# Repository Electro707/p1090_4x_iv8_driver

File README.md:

# P1090 - IV-8 Driver, 4x
\> PCBs (both), Rev 1
\> Firmware, Rev 1A (wip)
\> Enclosure, Rev 1

This project is a driver for 4xIV-8 VFD Tubes.

# Directory Structure
- E1091: PCB, Driver board, KiCAD
- E1092: PCB, IV-8 Adapter Board, KiCAD
- F1093: Firmware, Arduino-IDE
- CAD: Enclosure, FreeCAD. All parts are under `C1094.FCStd`
    - C1094: Bottom Enclosure
    - C1095: Top Enclosure
    - C1096: Button Press Extender
    - C1097: Light Pipe for LED
- `release`: Latest exported build files, includes Schematic, BOM, Gerber, and STL files

# Firmware Doc

The document for the firmware can be found over at [https://electro707.com/documentation/Projects/F1093_docs/](https://electro707.com/documentation/Projects/F1093_docs/)

The document also describes the requirements for building the Firmware through the Arduino IDE.

To build the firmware, you will need to make a file `wifiDefault.h` in the firmrware's folder with the following WIFI credentials

```c
#ifndef WIFI_DEFAULT_H
#define WIFI_DEFAULT_H

#define DEFAULT_WIFI_SSID       "ENTER-SSID"
#define DEFAULT_WIFI_PASSWORD   "ENTER_PASS"

#endif
```

# Known Issues
> [!IMPORTANT]
> Please read the file linked below before attempting to build this hardware.

Known issues, and any workarounds, are documented in [ERRATA.md](ERRATA.md).

# todo:
- Buy or 3D print light-pipes for better LED-to-IV8 conductance

# License
This project is licensed under [GPLv3](LICENSE.md)**

** This excludes the files in `E1091_PCB_Driver/ExternalStep`, as they came from the manufacturer.

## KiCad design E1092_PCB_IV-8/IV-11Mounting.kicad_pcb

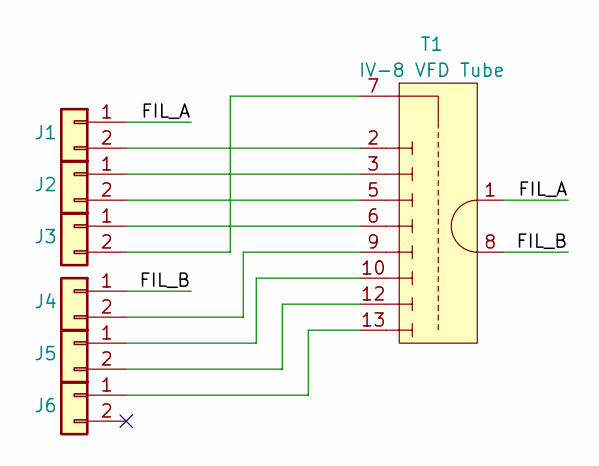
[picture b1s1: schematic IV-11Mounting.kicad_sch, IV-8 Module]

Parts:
J1, J2, J3, J4, J5, J6: Conn_01x02; PinHeader_1x02_P2.54mm_Vertical
T1: IV-8 VFD Tube; IV-8 VFD

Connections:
/FIL_A: J1.1, T1.1
/FIL_B: J4.1, T1.8
unnamed: J1.2, T1.2
unnamed: J2.1, T1.3
unnamed: J2.2, T1.5
unnamed: J3.1, T1.6
unnamed: J3.2, T1.7
unnamed: J4.2, T1.9
unnamed: J5.1, T1.10
unnamed: J5.2, T1.12
unnamed: J6.1, T1.13

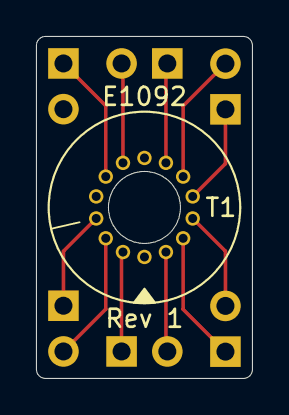
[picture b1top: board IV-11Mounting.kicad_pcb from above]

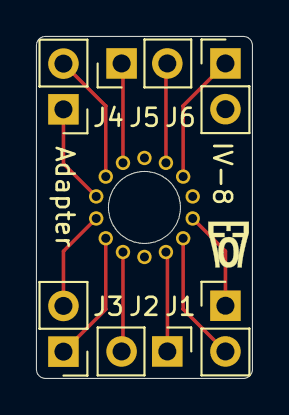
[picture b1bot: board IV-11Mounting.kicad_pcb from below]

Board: 2 copper layers, 12.0 x 19.0 mm, 7 parts (6 on the bottom side), 11 nets.

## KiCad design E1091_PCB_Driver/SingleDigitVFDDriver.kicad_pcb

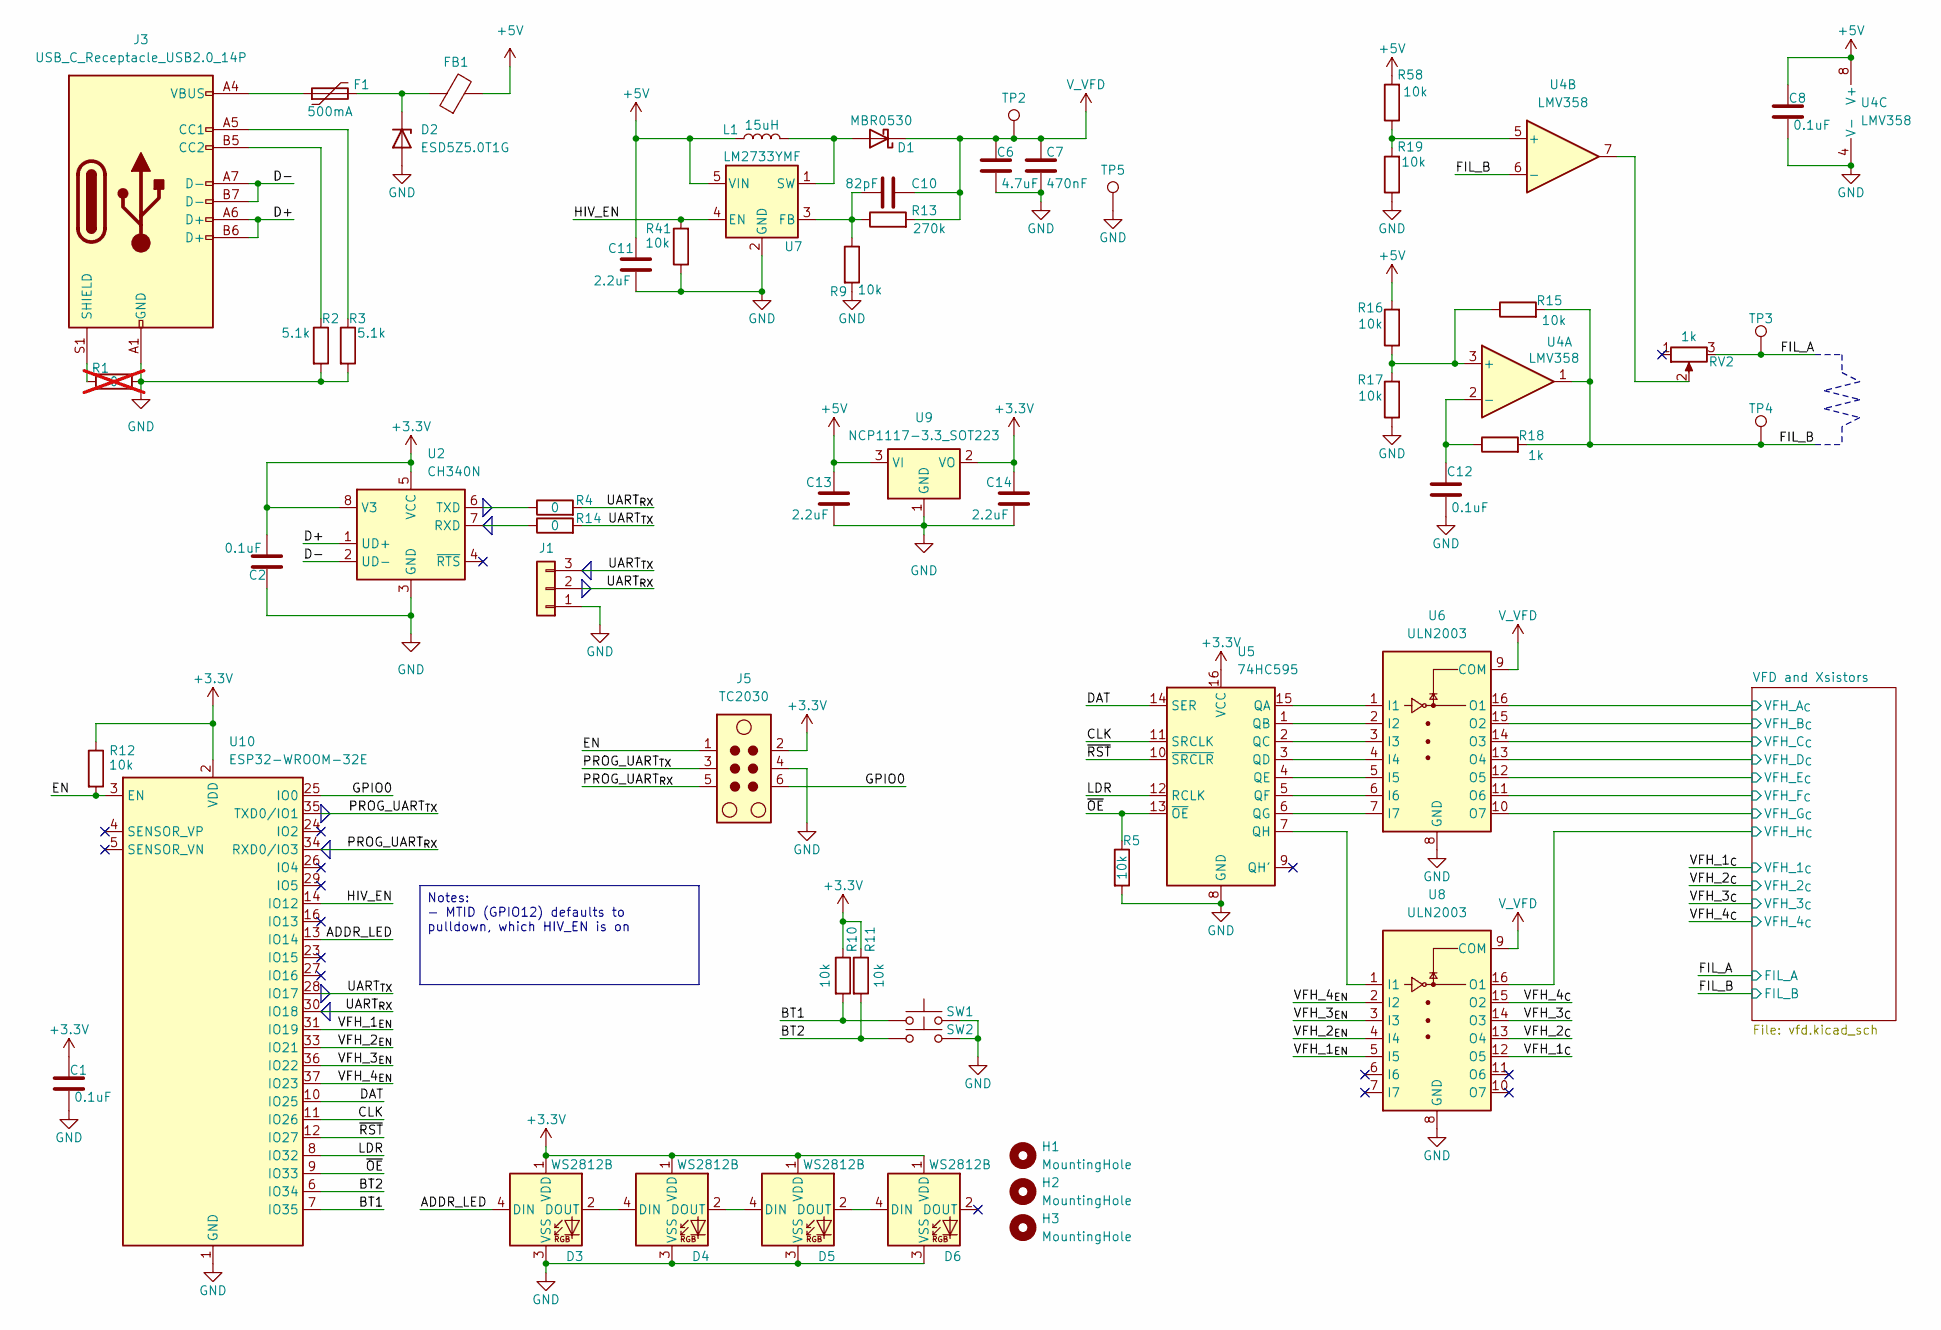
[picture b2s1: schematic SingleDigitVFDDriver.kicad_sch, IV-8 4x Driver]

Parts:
C1, C2, C8, C12: 0.1uF; C_0805_2012Metric
C6: 4.7uF; C_1206_3216Metric
C7: 470nF; C_0805_2012Metric
C10: 82pF; C_0805_2012Metric
C11, C13, C14: 2.2uF; C_0805_2012Metric
D1: MBR0530; D_SOD-123
D2: ESD5Z5.0T1G; D_SOD-523
D3, D4, D5, D6: WS2812B; LED_WS2812B_PLCC4_5.0x5.0mm_P3.2mm
F1: 500mA; Fuse_1206_3216Metric
FB1: FerriteBead; L_0805_2012Metric
H1, H2, H3: MountingHole; MountingHole_3.2mm_M3_DIN965
J1: Conn_01x03; PinSocket_1x03_P2.54mm_Vertical
J3: USB_C_Receptacle_USB2.0_14P; USB_C_Receptacle_GCT_USB4085
J5: TC2030; Tag-Connect_TC2030-IDC-NL_2x03_P1.27mm_Vertical
L1: 15uH; L_1210_3225Metric
R1: 0; R_0805_2012Metric; not fitted
R2, R3: 5.1k; R_0805_2012Metric
R4, R14: 0; R_0805_2012Metric
R5, R9, R10, R11, R12, R15, R16, R17, R19, R41, R58: 10k; R_0805_2012Metric
R13: 270k; R_0805_2012Metric
R18: 1k; R_0805_2012Metric
RV2: 1k; Potentiometer_Bourns_3266W_Vertical
SW1, SW2: SW_Push; SW_Tactile_SPST_Angled_PTS645Vx83-2LFS
TP2, TP3, TP4, TP5: TestPoint; TestPoint_Keystone_5005-5009_Compact
U2: CH340N; SOP-8_3.9x4.9mm_P1.27mm
U4: LMV358; SOIC-8_3.9x4.9mm_P1.27mm
U5: 74HC595; SOIC-16_3.9x9.9mm_P1.27mm
U6, U8: ULN2003; SOIC-16_3.9x9.9mm_P1.27mm
U7: LM2733YMF; SOT-23-5
U9: NCP1117-3.3_SOT223; SOT-223-3_TabPin2
U10: ESP32-WROOM-32E; ESP32-WROOM-32D

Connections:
+3.3V: C1.1, C2.2, C14.1, D3.1 (VDD), D4.1 (VDD), D5.1 (VDD), D6.1 (VDD), J5.2, R10.1, R11.1, R12.1, U2.5 (VCC), U2.8 (V3), U5.16 (VCC), U9.2 (VO), U10.2 (VDD)
+5V: C8.1, C11.1, C13.1, FB1.2, L1.1, R16.2, R58.2, U4.8 (V+), U7.5 (VIN), U9.3 (VI)
/ADDR_LED: D3.4 (DIN), U10.13 (IO14)
/BT1: R10.2, SW1.1, U10.7 (IO35)
/BT2: R11.2, SW2.1, U10.6 (IO34)
/CLK: U5.11 (SRCLK), U10.11 (IO26)
/D+: J3.A6 (D+), J3.B6 (D+), U2.1 (UD+)
/D-: J3.A7 (D-), J3.B7 (D-), U2.2 (UD-)
/DAT: U5.14 (SER), U10.10 (IO25)
/EN: J5.1, R12.2, U10.3 (EN)
/FIL_A: RV2.3, TP3.1; also elsewhere on the board
/FIL_B: R15.2, R18.2, TP4.1, U4.1, U4.6 (-); also elsewhere on the board
/GPIO0: J5.6, U10.25 (IO0)
/HIV_EN: R41.2, U7.4 (EN), U10.14 (IO12)
/LDR: U5.12 (RCLK), U10.8 (IO32)
/PROG_UART_{RX}: J5.5, U10.34 (RXD0/IO3)
/PROG_UART_{TX}: J5.3, U10.35 (TXD0/IO1)
/UART_{RX}: J1.2, R4.2, U10.30 (IO18)
/UART_{TX}: J1.3, R14.2, U10.28 (IO17)
/VFD and Xsistors/VFH_A_{C}: U6.16 (O1); also elsewhere on the board
/VFD and Xsistors/VFH_B_{C}: U6.15 (O2); also elsewhere on the board
/VFD and Xsistors/VFH_C_{C}: U6.14 (O3); also elsewhere on the board
/VFD and Xsistors/VFH_D_{C}: U6.13 (O4); also elsewhere on the board
/VFD and Xsistors/VFH_E_{C}: U6.12 (O5); also elsewhere on the board
/VFD and Xsistors/VFH_F_{C}: U6.11 (O6); also elsewhere on the board
/VFD and Xsistors/VFH_G_{C}: U6.10 (O7); also elsewhere on the board
/VFD and Xsistors/VFH_H_{C}: U8.16 (O1); also elsewhere on the board
/VFH_1_{C}: U8.12 (O5); also elsewhere on the board
/VFH_1_{EN}: U8.5 (I5), U10.31 (IO19)
/VFH_2_{C}: U8.13 (O4); also elsewhere on the board
/VFH_2_{EN}: U8.4 (I4), U10.33 (IO21)
/VFH_3_{C}: U8.14 (O3); also elsewhere on the board
/VFH_3_{EN}: U8.3 (I3), U10.36 (IO22)
/VFH_4_{C}: U8.15 (O2); also elsewhere on the board
/VFH_4_{EN}: U8.2 (I2), U10.37 (IO23)
/~OE: R5.1, U5.13 (~OE), U10.9 (IO33)
/~RST: U5.10 (~SRCLR), U10.12 (IO27)
GND: C1.2, C2.1, C6.2, C7.2, C8.2, C11.2, C12.2, C13.2, C14.2, D2.2 (A), D3.3 (VSS), D4.3 (VSS), D5.3 (VSS), D6.3 (VSS), J1.1, J3.A1 (GND), J3.A12 (GND), J3.B1 (GND), J3.B12 (GND), J5.4, R1.2, R2.2, R3.2, R5.2, R9.2, R17.1, R19.1, R41.1, SW1.2, SW2.2, TP5.1, U2.3 (GND), U4.4 (V-), U5.8 (GND), U6.8 (GND), U7.2 (GND), U8.8 (GND), U9.1 (GND), U10.1 (GND), U10.15 (GND), U10.38 (GND), U10.39 (GND); also elsewhere on the board
unnamed: D1.2 (A), L1.2, U7.1 (SW)
unnamed: D2.1 (K), F1.2, FB1.1
unnamed: D3.2 (DOUT), D4.4 (DIN)
unnamed: D4.2 (DOUT), D5.4 (DIN)
unnamed: D5.2 (DOUT), D6.4 (DIN)
unnamed: F1.1, J3.A4 (VBUS), J3.A9 (VBUS), J3.B4 (VBUS), J3.B9 (VBUS)
unnamed: J3.A5 (CC1), R3.1
unnamed: J3.B5 (CC2), R2.1
unnamed: J3.S1 (SHIELD), R1.1
unnamed: RV2.2, U4.7
unnamed: R14.1, U2.7 (RXD)
unnamed: R4.1, U2.6 (TXD)
unnamed: R15.1, R16.1, R17.2, U4.3 (+)
unnamed: C12.1, R18.1, U4.2 (-)
unnamed: R19.2, R58.1, U4.5 (+)
unnamed: U5.15 (QA), U6.1 (I1)
unnamed: U5.1 (QB), U6.2 (I2)
unnamed: U5.2 (QC), U6.3 (I3)
unnamed: U5.3 (QD), U6.4 (I4)
unnamed: U5.4 (QE), U6.5 (I5)
unnamed: U5.5 (QF), U6.6 (I6)
unnamed: U5.6 (QG), U6.7 (I7)
unnamed: U5.7 (QH), U8.1 (I1)
unnamed: C10.1, R9.1, R13.1, U7.3 (FB)
V_VFD: C6.1, C7.1, C10.2, D1.1 (K), R13.2, TP2.1, U6.9 (COM), U8.9 (COM); also elsewhere on the board

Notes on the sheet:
Notes: - MTID (GPIO12) defaults to pulldown, which HIV_EN is on

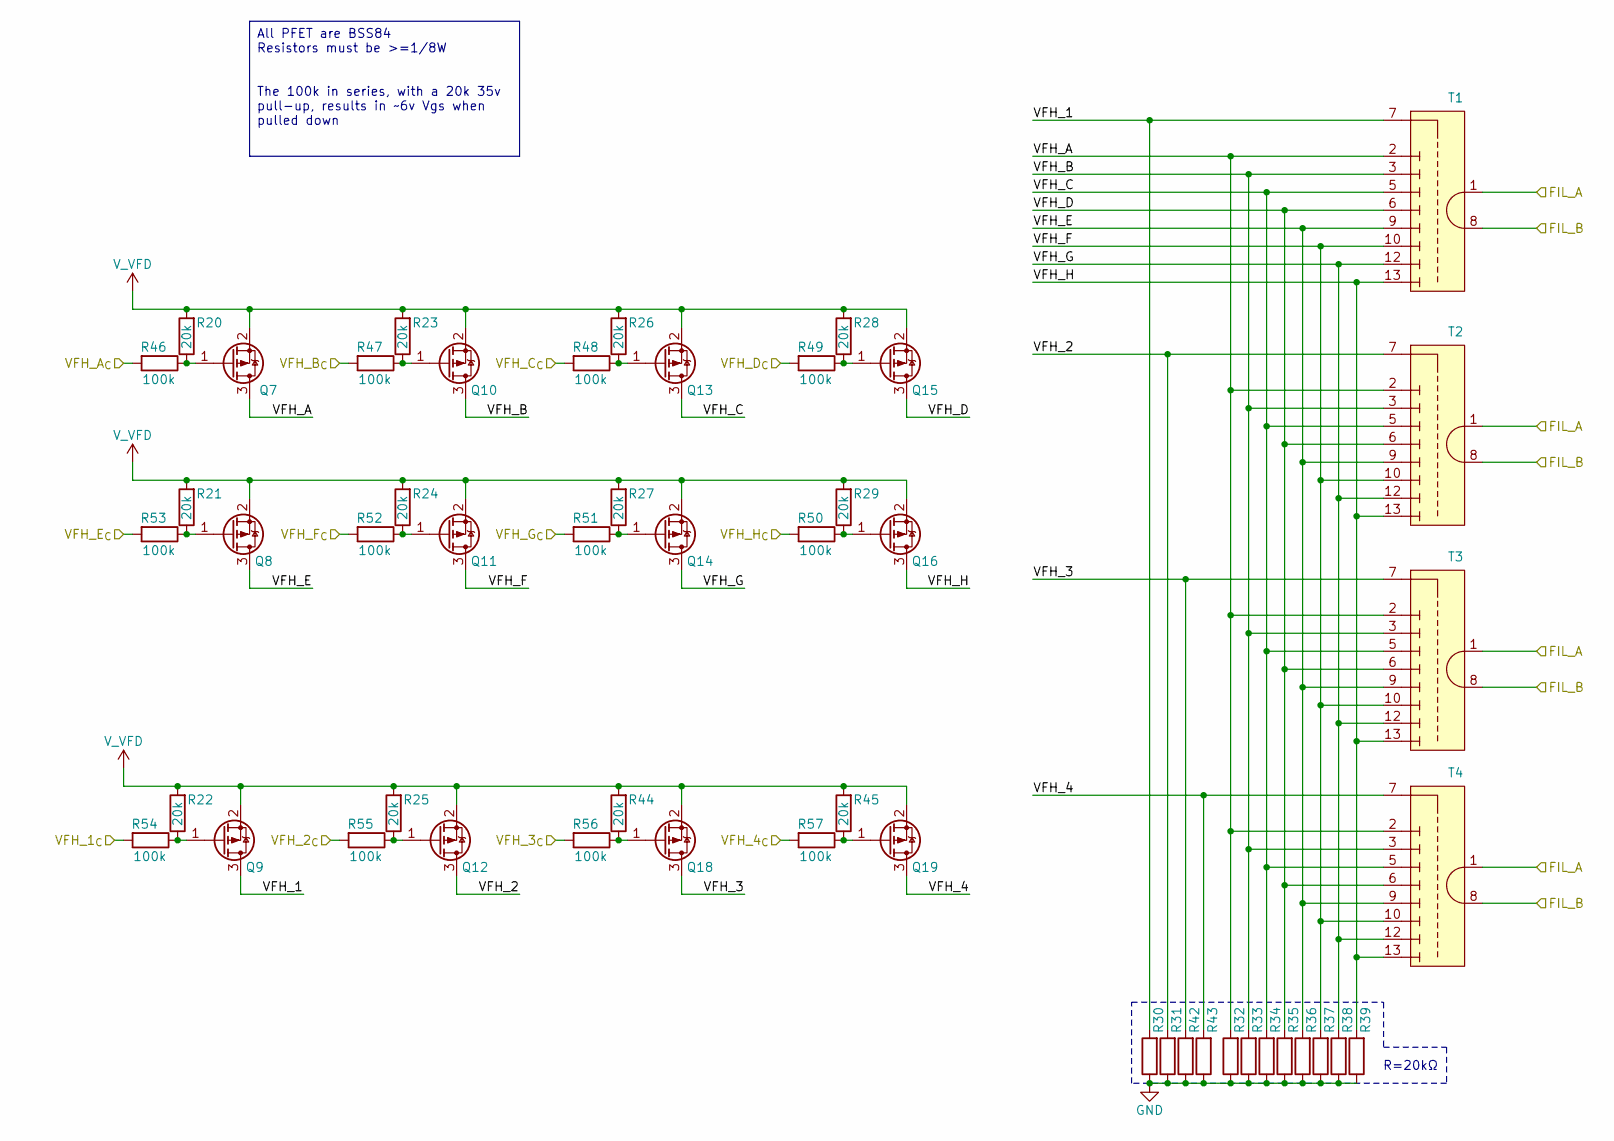
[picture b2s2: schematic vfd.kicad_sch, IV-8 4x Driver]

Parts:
Q7, Q8, Q9, Q10, Q11, Q12, Q13, Q14, Q15, Q16, Q18, Q19: BSS84; SOT-23
R20, R21, R22, R23, R24, R25, R26, R27, R28, R29, R30, R31, R32, R33, R34, R35, R36, R37, R38, R39, R42, R43, R44, R45: 20k; R_0805_2012Metric
R46, R47, R48, R49, R50, R51, R52, R53, R54, R55, R56, R57: 100k; R_0805_2012Metric
T1, T2, T3, T4: IV-8 Adapter

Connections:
/FIL_A: T1.1, T2.1, T3.1, T4.1; also elsewhere on the board
/FIL_B: T1.8, T2.8, T3.8, T4.8; also elsewhere on the board
/VFD and Xsistors/VFH_1: Q9.3 (D), R30.2, T1.7
/VFD and Xsistors/VFH_2: Q12.3 (D), R31.2, T2.7
/VFD and Xsistors/VFH_3: Q18.3 (D), R42.2, T3.7
/VFD and Xsistors/VFH_4: Q19.3 (D), R43.2, T4.7
/VFD and Xsistors/VFH_A: Q7.3 (D), R32.2, T1.2, T2.2, T3.2, T4.2
/VFD and Xsistors/VFH_A_{C}: R46.2; also elsewhere on the board
/VFD and Xsistors/VFH_B: Q10.3 (D), R33.2, T1.3, T2.3, T3.3, T4.3
/VFD and Xsistors/VFH_B_{C}: R47.2; also elsewhere on the board
/VFD and Xsistors/VFH_C: Q13.3 (D), R34.2, T1.5, T2.5, T3.5, T4.5
/VFD and Xsistors/VFH_C_{C}: R48.2; also elsewhere on the board
/VFD and Xsistors/VFH_D: Q15.3 (D), R35.2, T1.6, T2.6, T3.6, T4.6
/VFD and Xsistors/VFH_D_{C}: R49.2; also elsewhere on the board
/VFD and Xsistors/VFH_E: Q8.3 (D), R36.2, T1.9, T2.9, T3.9, T4.9
/VFD and Xsistors/VFH_E_{C}: R53.2; also elsewhere on the board
/VFD and Xsistors/VFH_F: Q11.3 (D), R37.2, T1.10, T2.10, T3.10, T4.10
/VFD and Xsistors/VFH_F_{C}: R52.2; also elsewhere on the board
/VFD and Xsistors/VFH_G: Q14.3 (D), R38.2, T1.12, T2.12, T3.12, T4.12
/VFD and Xsistors/VFH_G_{C}: R51.2; also elsewhere on the board
/VFD and Xsistors/VFH_H: Q16.3 (D), R39.2, T1.13, T2.13, T3.13, T4.13
/VFD and Xsistors/VFH_H_{C}: R50.2; also elsewhere on the board
/VFH_1_{C}: R54.2; also elsewhere on the board
/VFH_2_{C}: R55.2; also elsewhere on the board
/VFH_3_{C}: R56.2; also elsewhere on the board
/VFH_4_{C}: R57.2; also elsewhere on the board
GND: R30.1, R31.1, R32.1, R33.1, R34.1, R35.1, R36.1, R37.1, R38.1, R39.1, R42.1, R43.1; also elsewhere on the board
unnamed: Q7.1 (G), R20.1, R46.1
unnamed: Q8.1 (G), R21.1, R53.1
unnamed: Q9.1 (G), R22.1, R54.1
unnamed: Q10.1 (G), R23.1, R47.1
unnamed: Q11.1 (G), R24.1, R52.1
unnamed: Q12.1 (G), R25.1, R55.1
unnamed: Q13.1 (G), R26.1, R48.1
unnamed: Q14.1 (G), R27.1, R51.1
unnamed: Q15.1 (G), R28.1, R49.1
unnamed: Q16.1 (G), R29.1, R50.1
unnamed: Q18.1 (G), R44.1, R56.1
unnamed: Q19.1 (G), R45.1, R57.1
V_VFD: Q7.2 (S), Q8.2 (S), Q9.2 (S), Q10.2 (S), Q11.2 (S), Q12.2 (S), Q13.2 (S), Q14.2 (S), Q15.2 (S), Q16.2 (S), Q18.2 (S), Q19.2 (S), R20.2, R21.2, R22.2, R23.2, R24.2, R25.2, R26.2, R27.2, R28.2, R29.2, R44.2, R45.2; also elsewhere on the board

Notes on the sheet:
R=20kΩ
All PFET are BSS84 Resistors must be >=1/8W The 100k in series, with a 20k 35v pull-up, results in ~6v Vgs when pulled down

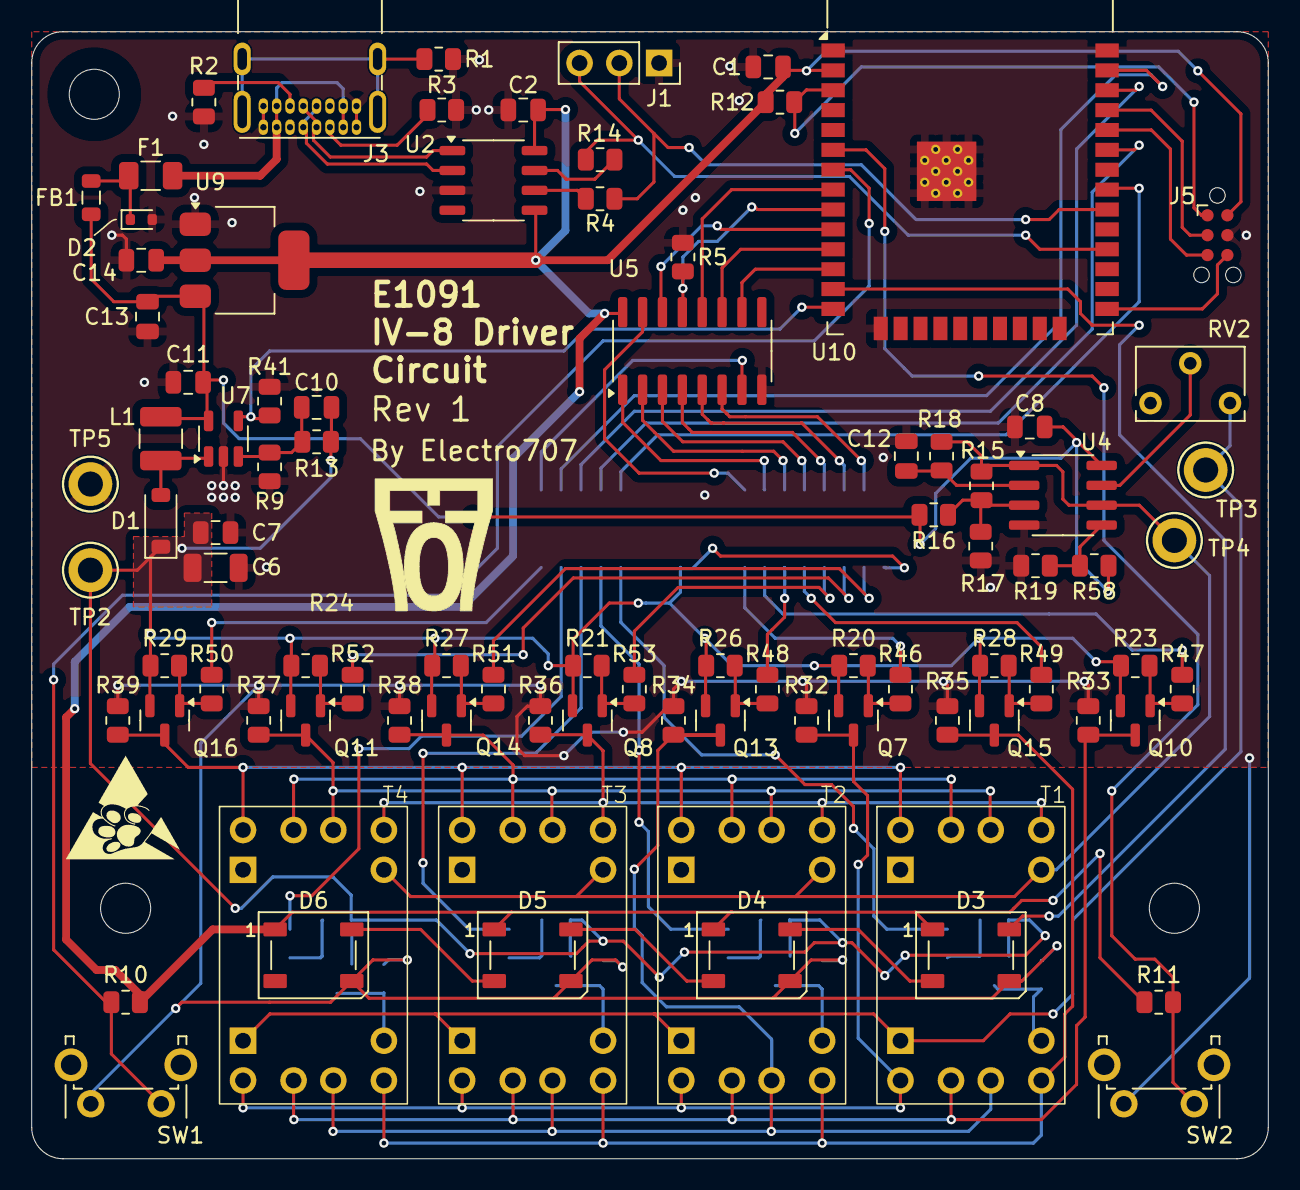
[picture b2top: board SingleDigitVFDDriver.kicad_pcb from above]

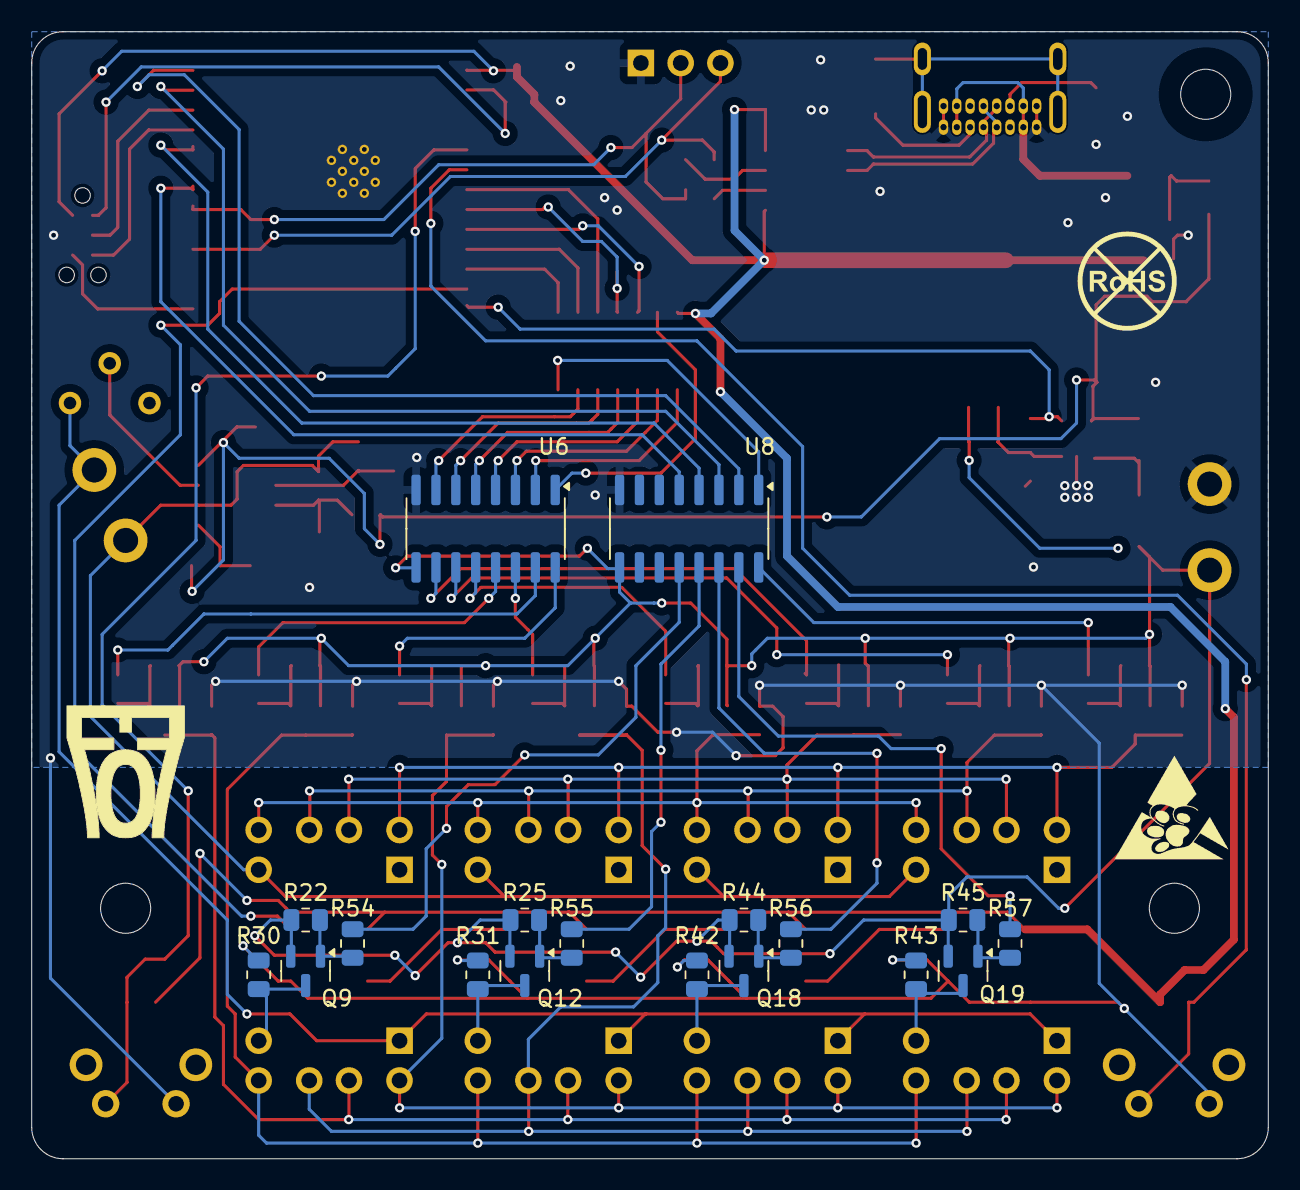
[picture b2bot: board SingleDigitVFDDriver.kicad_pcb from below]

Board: 2 copper layers, 79.0 x 72.0 mm, 110 parts (18 on the bottom side), 87 nets.

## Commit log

2025-05-03 Initial Release
2025-05-03 Fix readme
2025-07-12 heavy firmware work/modification
2025-07-15 added time formats: 24hr, 12hr, and metric un-commented code I commented for testing remove un-used comments
2025-07-15 Added link to firmware docs
2025-07-19 Renamed file
2025-07-19 Renamed B prefix to C for exported parts
2025-07-30 Added button piece to be able to press the buttons
2025-10-05 Started testing light-pipe
2026-01-05 Added errata document, describing the op-amp fix
2026-01-13 updated SPI to use registers directly made ISR to run from IRAM added LED Modes and LED color config Updated Docs
2026-01-13 Fixed doc
2026-01-19 Fixed no-blink mode. improved ws2812 flickering issue
2026-02-16 Fixed BOM diode to correct one
2026-02-16 Added new errata note. Added a design notes doc
